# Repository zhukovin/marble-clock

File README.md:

# marble-clock

https://engineezy.com/products/the-tipping-marble-clock

1. 11 3x10x4 bearings: https://a.co/d/4JFZjME
1. M3 Screw Kit: https://a.co/d/3sWPaf0
1. 32 0.5in ball bearings: https://a.co/d/eDzJ6P2
1. Nema 17 Motor: https://a.co/d/04mfYYL
1. 1 GT2 Pulley: https://a.co/d/fuRD2cA
1. A4988 Stepper Motor Driver: https://a.co/d/fOQgJpc
1. Wemos d1 mini ESP8266: https://a.co/d/8dCLFfo
1. Silicone grease: https://a.co/d/iCrpBB1

https://www.youtube.com/watch?v=GmLEBhJY5ks

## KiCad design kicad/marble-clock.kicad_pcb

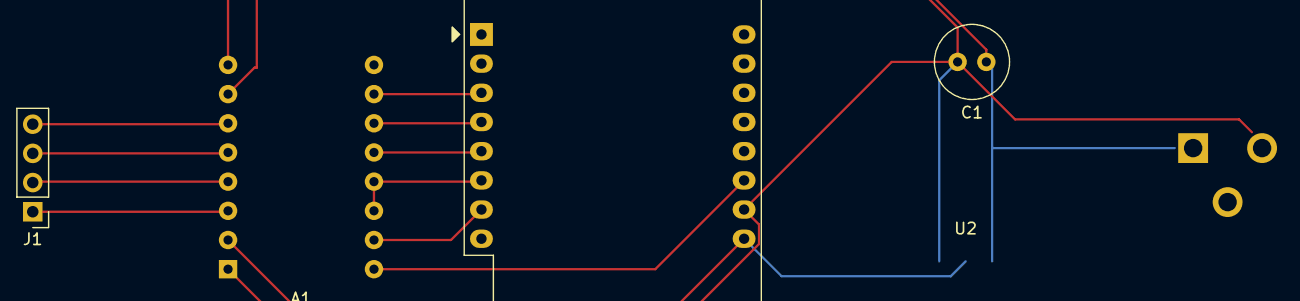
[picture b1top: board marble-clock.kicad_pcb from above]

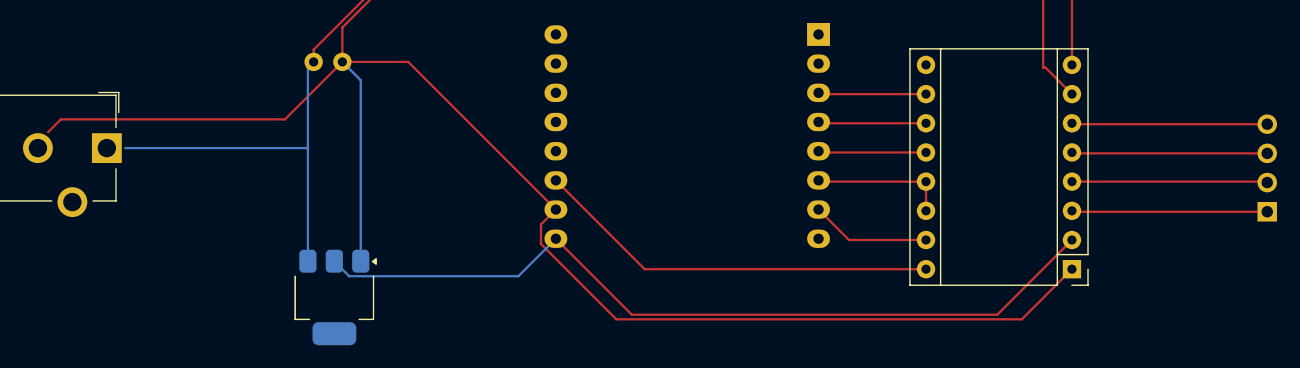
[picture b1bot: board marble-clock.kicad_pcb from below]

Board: 2 copper layers, 5 parts (2 on the bottom side), 13 nets.

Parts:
A1: HiLetgo A4988; Pololu_Breakout-16_15.2x20.3mm
C1: 220mF 16v; C_Radial_D6.3mm_H11.0mm_P2.50mm
J1: Conn_01x04_Pin M20-9990445; PinHeader_1x04_P2.54mm_Vertical
U1: WEMOS_D1_mini; WEMOS_D1_mini_light
U2: AMS1117-5.0; SOT-223-3_TabPin2

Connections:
+12V: A1.8 (VMOT), C1.1, U2.3 (VI)
/A+: A1.3 (1B), J1.1
/A-: A1.4 (1A), J1.2
/B+: A1.6 (2B), J1.4
/B-: A1.5 (2A), J1.3
GND: A1.1 (GND), A1.7 (GND), C1.2, U1.10 (GND), U2.1 (GND)
unnamed: A1.16 (DIR), U1.11 (D4)
unnamed: A1.10 (MS1), U1.3 (D0)
unnamed: A1.11 (MS2), U1.4 (SCK/D5)
unnamed: A1.12 (MS3), U1.5 (MISO/D6)
unnamed: A1.15 (STEP), U1.7 (CS/D8)
unnamed: A1.2 (VDD), U1.9 (5V), U2.2 (VO)
unnamed: A1.13 (~RESET), A1.14 (~SLEEP), U1.6 (MOSI/D7)

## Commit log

2025-09-19 Initial version
2025-09-19 Add BOM and links
2025-09-19 Fix list in readme
2025-09-19 Add motor data sheet
2025-09-19 Add PCB photos
2025-09-20 Add Arduino code
